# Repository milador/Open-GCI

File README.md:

# Open-GCI

An open-source accessible gaming interface that enables those with limited or no hand movement to play their favourite console based game using more accessible input methods.
Adaptive switches and USB keyboards are currently the two input methods that can be used to play console based games.

# Downloads 

These are all the files and documentation associated with the Open-GCI project.

 <table style="width:100%">
  <tr>
    <th>Resource</th>
    <th>Version</th>
    <th>Format</th>
    <th>Link</th>
  </tr>
    <tr>
    <td>Open-GCI All</td>
    <td>1.0</td>
    <td>ZIP</td>
    <td><a href="https://github.com/milador/Open-GCI/archive/master.zip">Open-GCI-master.zip</a></td>
  </tr>
  <tr>
    <td>Open-GCI Manual</td>
    <td></td>
    <td>PDF</td>
    <td></td>
  </tr>
  <tr>
    <td>Open-GCI BOM (XLSX)</td>
    <td>October 6, 2018</td>
    <td>XLSX</td>
    <td><a href="https://github.com/milador/Open-GCI/raw/master/Open-GCI_BOM.xlsx">Open-GCI_BOM.xlsx</a></td>
  </tr>
  <tr>
    <td>Open-GCI Keyboard code</td>
    <td>1.0</td>
    <td>Py</td>
    <td><a href="https://github.com/milador/Open-GCI/raw/master/Software/gci_keyboard.py">gci_keyboard.py</a></td>
  </tr>
  <tr>
    <td>Open-GCI Board Layout</td>
    <td>1.0</td>
    <td>BRD</td>
    <td><a href="https://raw.githubusercontent.com/milador/Open-GCI/master/Hardware/PCB_design/Open-GCI.brd">Open-GCI.brd</a></td>
  </tr>
  <tr>
    <td>Open-GCI Board Schematic</td>
    <td>1.0</td>
    <td>SCH</td>
    <td><a href="https://raw.githubusercontent.com/milador/Open-GCI/master/Hardware/PCB_design/Open-GCI.sch">Open-GCI.sch</a></td>
  </tr>
</table> 

# Diagram

The following diagram represents the hardware of the Open-GCI interface.

# Installation 

## Hardware Setup Instructions

Coming soon..

## Software Setup Instructions

  1. Install Raspbian on an SD card according to the official documents 

https://www.raspberrypi.org/documentation/installation/installing-images/

2.	Download Dependencies

  2.1. Startup the raspberrypi zero W
  
  2.2. Open the command line
  
  2.3. Install the necessary packages
```
sudo apt-get update
sudo apt-get install build-essential python-dev python-pip git scons swig
sudo pip install RPi.GPIO
```

3.	Compile & Install rpi_ws281x Library
  
  3.1. Download the library source and compile it using following command : 
``` 
git clone https://github.com/jgarff/rpi_ws281x.git
cd rpi_ws281x
scons
``` 
  3.2. Install the Python library by executing following command : 
``` 
cd python
sudo python setup.py install
``` 
  
4.	Download gci_keyboard.py
  
  4.1. Open the command line
  
  4.2. Enter the pi directory
  
  4.3. Create a new python file using nano and name it gci_keyboard.py using following command: ```sudo nano gci_keyboar.py``` 
  
  4.4. Copy and paste the keyboard code from Software/gci_keyboard.py 
  
  4.5. Save the file and exit nano
  
5. Run code on bootup

  5.1. Open /etc/rc.local using nano by running following command: ```sudo nano /etc/rc.local```
  
  5.2. Add the following line on its own line right before exit 0: ```sudo python /home/pi/gci_keyboard.py  &```
  
  5.3. Save and exit /etc/rc.local
  
  5.4. Reboot the raspberrypi zero W by running following command: ```sudo shutdown -r now```
  
6.	Varify software is running 
  
   6.1. The Led will change color from Blue to Green when the software is ready to use

# PS4 to keyboard button mapping 

# Picture 

# License

## Creative Commons Attribution-NonCommercial-ShareAlike (CC-BY-NC-SA)

Copyright (c) 2018 Milador

A creative commons license that bans commercial use and requires you to release any modified works under this license.

<br />This work is licensed under a <a rel="license" href="http://creativecommons.org/licenses/by-nc-sa/3.0/">Creative Commons Attribution-NonCommercial-ShareAlike 3.0 Unported License</a>.

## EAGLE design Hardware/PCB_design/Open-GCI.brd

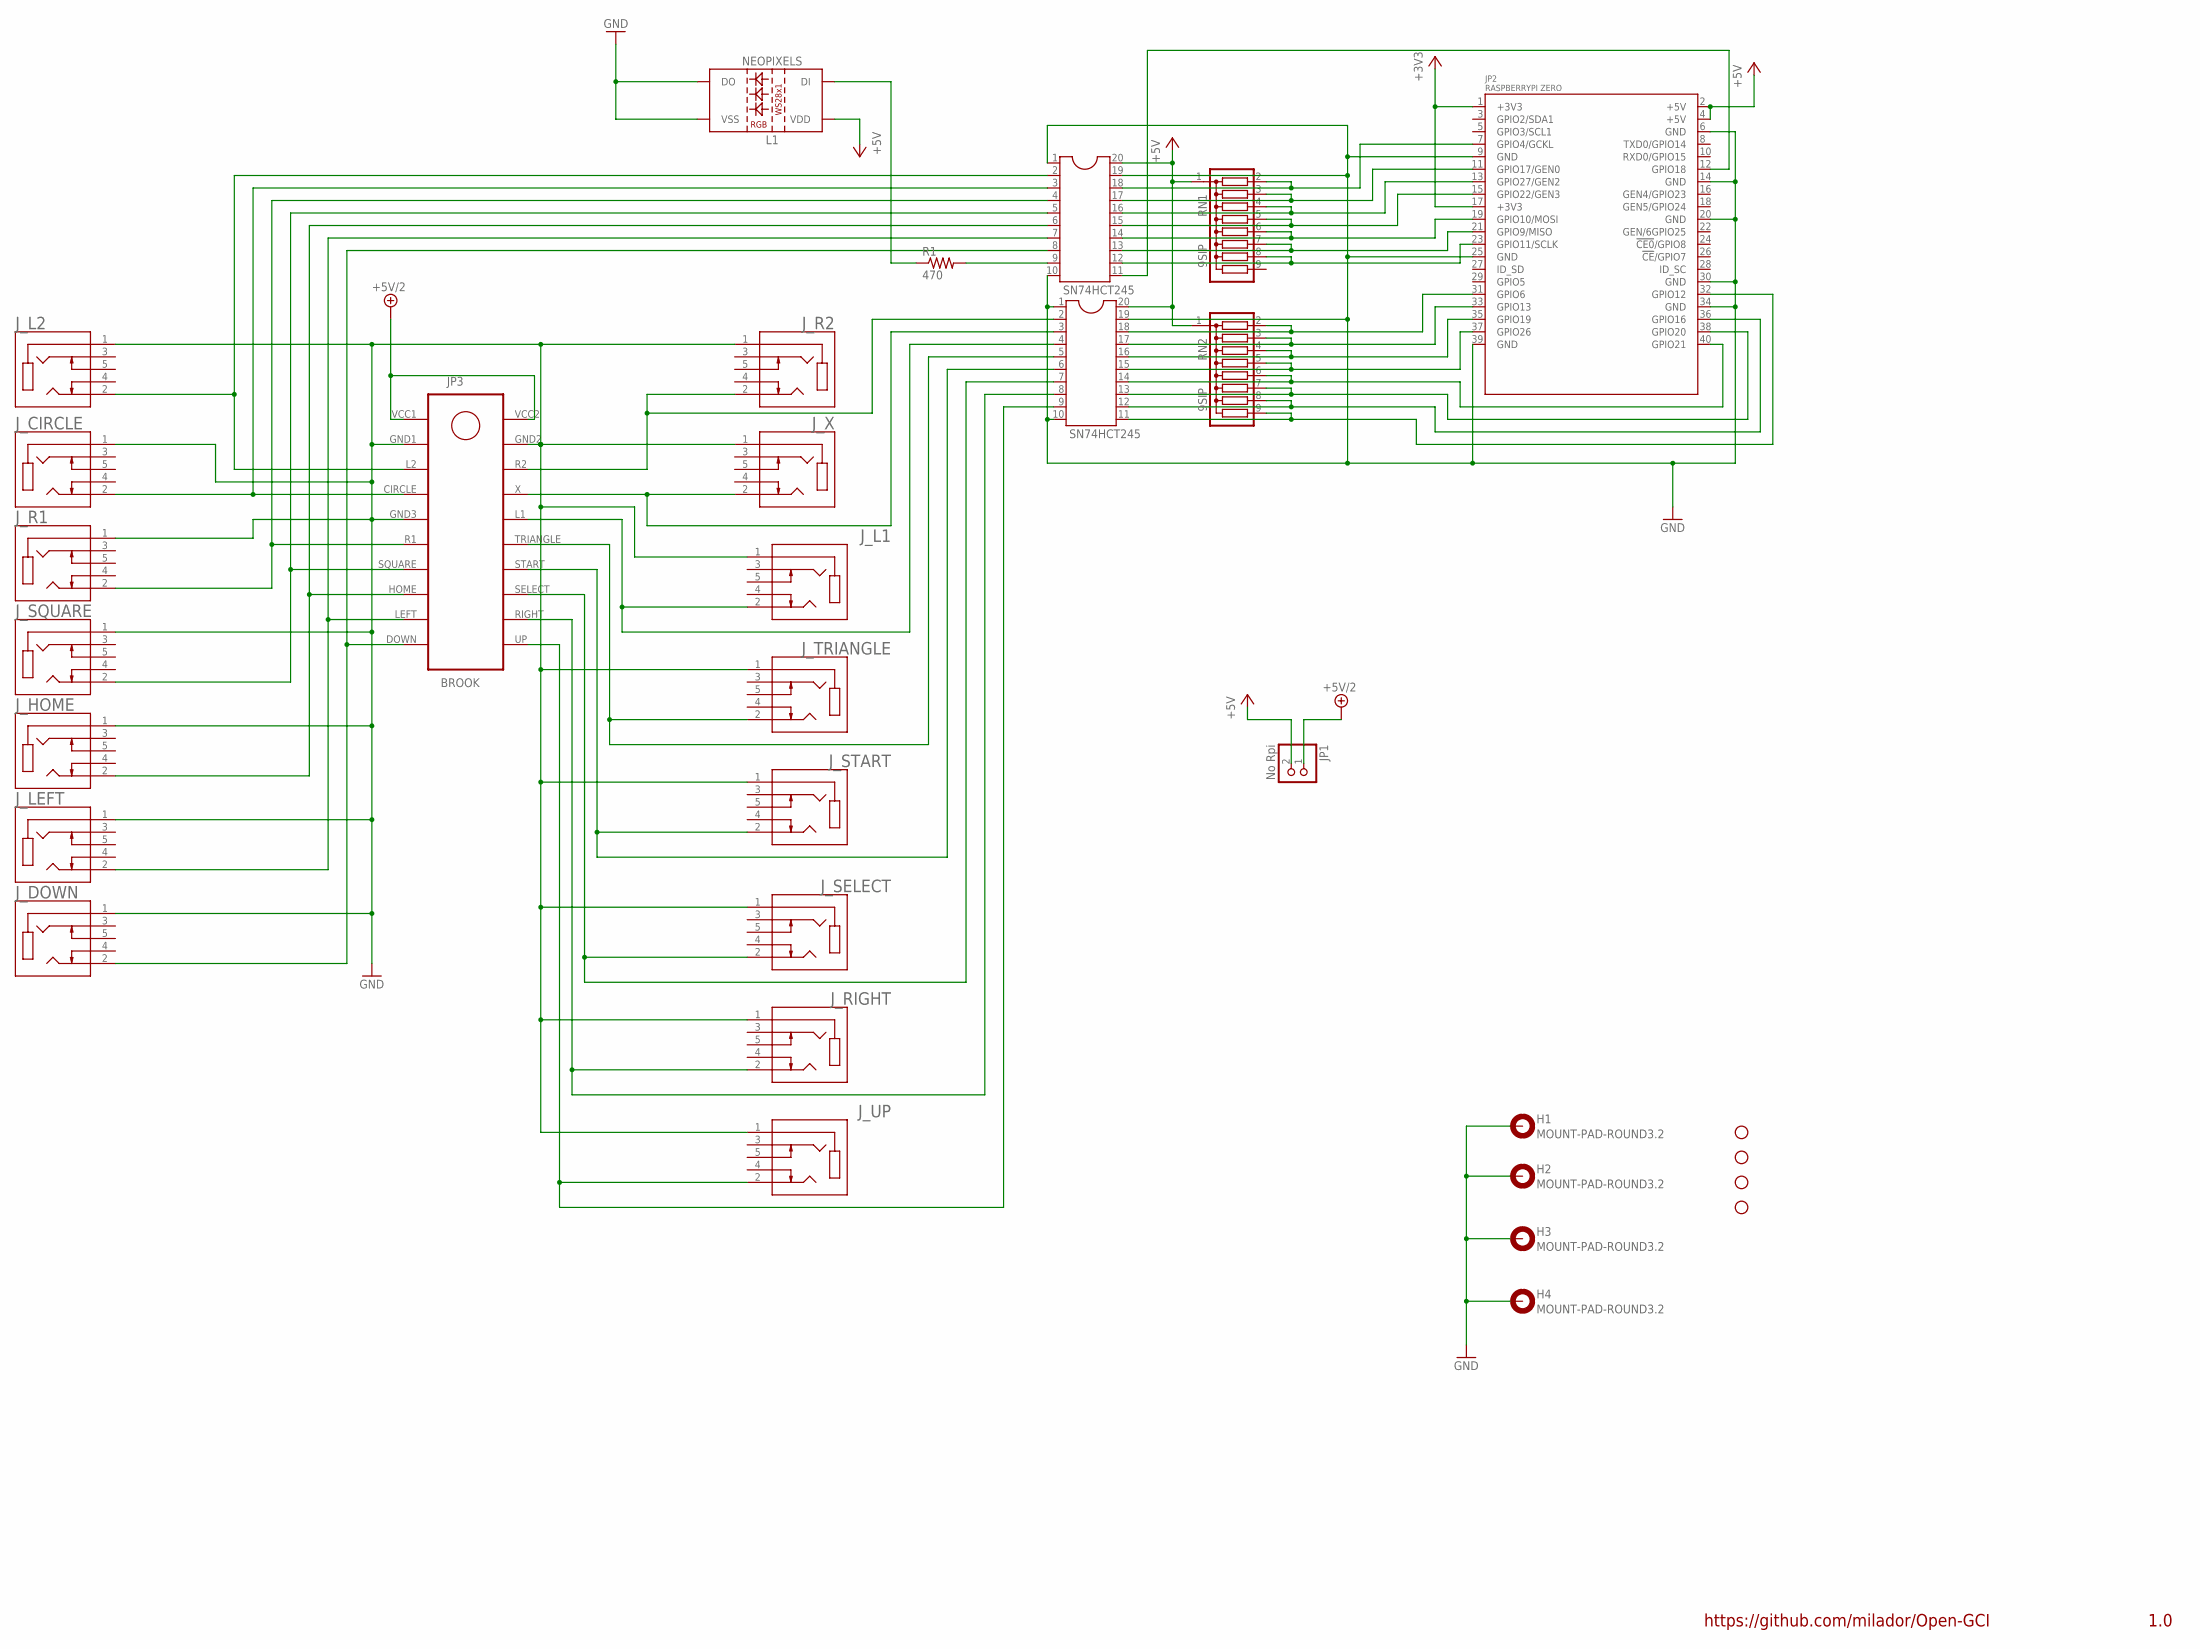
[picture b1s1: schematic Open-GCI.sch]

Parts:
H1, H2, H3, H4: MOUNT-PAD-ROUND3.2; 3,2-PAD
H5, H6, H7, H8: STAND-OFF
IC1, IC2: SN74HCT245
JP1: No Rpi; 1X02
JP2: RASPBERRYPI ZERO; RASPBERRYPI_ZERO
JP3: BROOK; CONN_2X10
J_CIRCLE: SJ1-3535NG; CUI_SJ1-3535NG
J_DOWN: SJ1-3535NG; CUI_SJ1-3535NG
J_HOME: SJ1-3535NG; CUI_SJ1-3535NG
J_L1, J_L2: SJ1-3535NG; CUI_SJ1-3535NG
J_LEFT: SJ1-3535NG; CUI_SJ1-3535NG
J_R1, J_R2: SJ1-3535NG; CUI_SJ1-3535NG
J_RIGHT: SJ1-3535NG; CUI_SJ1-3535NG
J_SELECT: SJ1-3535NG; CUI_SJ1-3535NG
J_SQUARE: SJ1-3535NG; CUI_SJ1-3535NG
J_START: SJ1-3535NG; CUI_SJ1-3535NG
J_TRIANGLE: SJ1-3535NG; CUI_SJ1-3535NG
J_UP: SJ1-3535NG; CUI_SJ1-3535NG
J_X: SJ1-3535NG; CUI_SJ1-3535NG
L1: NEOPIXELS; NEOPIXELS-5MM
R1: 470; 0204/7
RN1, RN2: 9SIP; SIL9

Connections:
+3V3: JP2.1 (+3V3), JP2.17 (+3V3)
+5V: IC1.20, IC2.20, JP1.2, JP2.2 (+5V), JP2.4 (+5V), L1.2 (VDD), RN1.1, RN2.1
+5V/2: JP1.1, JP3.VCC1, JP3.VCC2
GND: H1.B3,2, H2.B3,2, H3.B3,2, H4.B3,2, IC1.1, IC1.10, IC1.19, IC2.1, IC2.10, IC2.19, JP2.6 (GND), JP2.9 (GND), JP2.14 (GND), JP2.20 (GND), JP2.25 (GND), JP2.30 (GND), JP2.34 (GND), JP2.39 (GND), JP3.GND1, JP3.GND2, JP3.GND3, J_CIRCLE.1, J_DOWN.1, J_HOME.1, J_L1.1, J_L2.1, J_LEFT.1, J_R1.1, J_R2.1, J_RIGHT.1, J_SELECT.1, J_SQUARE.1, J_START.1, J_TRIANGLE.1, J_UP.1, J_X.1, L1.3 (VSS), L1.4 (DO)
unnamed: IC1.9, R1.2
unnamed: L1.1 (DI), R1.1
NGP7: IC1.18, JP2.7 (GPIO4/GCKL), RN1.2
NGP11: IC1.17, JP2.11 (GPIO17/GEN0), RN1.3
NGP12: IC1.11, JP2.12 (GPIO18)
NGP13: IC1.16, JP2.13 (GPIO27/GEN2), RN1.4
NGP15: IC1.15, JP2.15 (GPIO22/GEN3), RN1.5
NGP19: IC1.14, JP2.19 (GPIO10/MOSI), RN1.6
NGP21: IC1.13, JP2.21 (GPIO9/MISO), RN1.7
NGP23: IC1.12, JP2.23 (GPIO11/SCLK), RN1.8
NGP31: IC2.18, JP2.31 (GPIO6), RN2.2
NGP32: IC2.11, JP2.32 (GPIO12), RN2.9
NGP33: IC2.17, JP2.33 (GPIO13), RN2.3
NGP35: IC2.16, JP2.35 (GPIO19), RN2.4
NGP36: IC2.12, JP2.36 (GPIO16), RN2.8
NGP37: IC2.15, JP2.37 (GPIO26), RN2.5
NGP38: IC2.13, JP2.38 (GPIO20), RN2.7
NGP40: IC2.14, JP2.40 (GPIO21), RN2.6
NJ_CIR: IC1.3, JP3.CIRCLE, J_CIRCLE.2
NJ_DOWN: IC1.8, JP3.DOWN, J_DOWN.2
NJ_HOME: IC1.6, JP3.HOME, J_HOME.2
NJ_L1: IC2.4, JP3.L1, J_L1.2
NJ_L2: IC1.2, JP3.L2, J_L2.2
NJ_LEFT: IC1.7, JP3.LEFT, J_LEFT.2
NJ_R1: IC1.4, JP3.R1, J_R1.2
NJ_R2: IC2.2, JP3.R2, J_R2.2
NJ_RIGHT: IC2.8, JP3.RIGHT, J_RIGHT.2
NJ_SELECT: IC2.7, JP3.SELECT, J_SELECT.2
NJ_SQU: IC1.5, JP3.SQUARE, J_SQUARE.2
NJ_START: IC2.6, JP3.START, J_START.2
NJ_TRI: IC2.5, JP3.TRIANGLE, J_TRIANGLE.2
NJ_UP: IC2.9, JP3.UP, J_UP.2
NJ_X: IC2.3, JP3.X, J_X.2

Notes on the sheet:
https://github.com/milador/Open-GCI
1.0

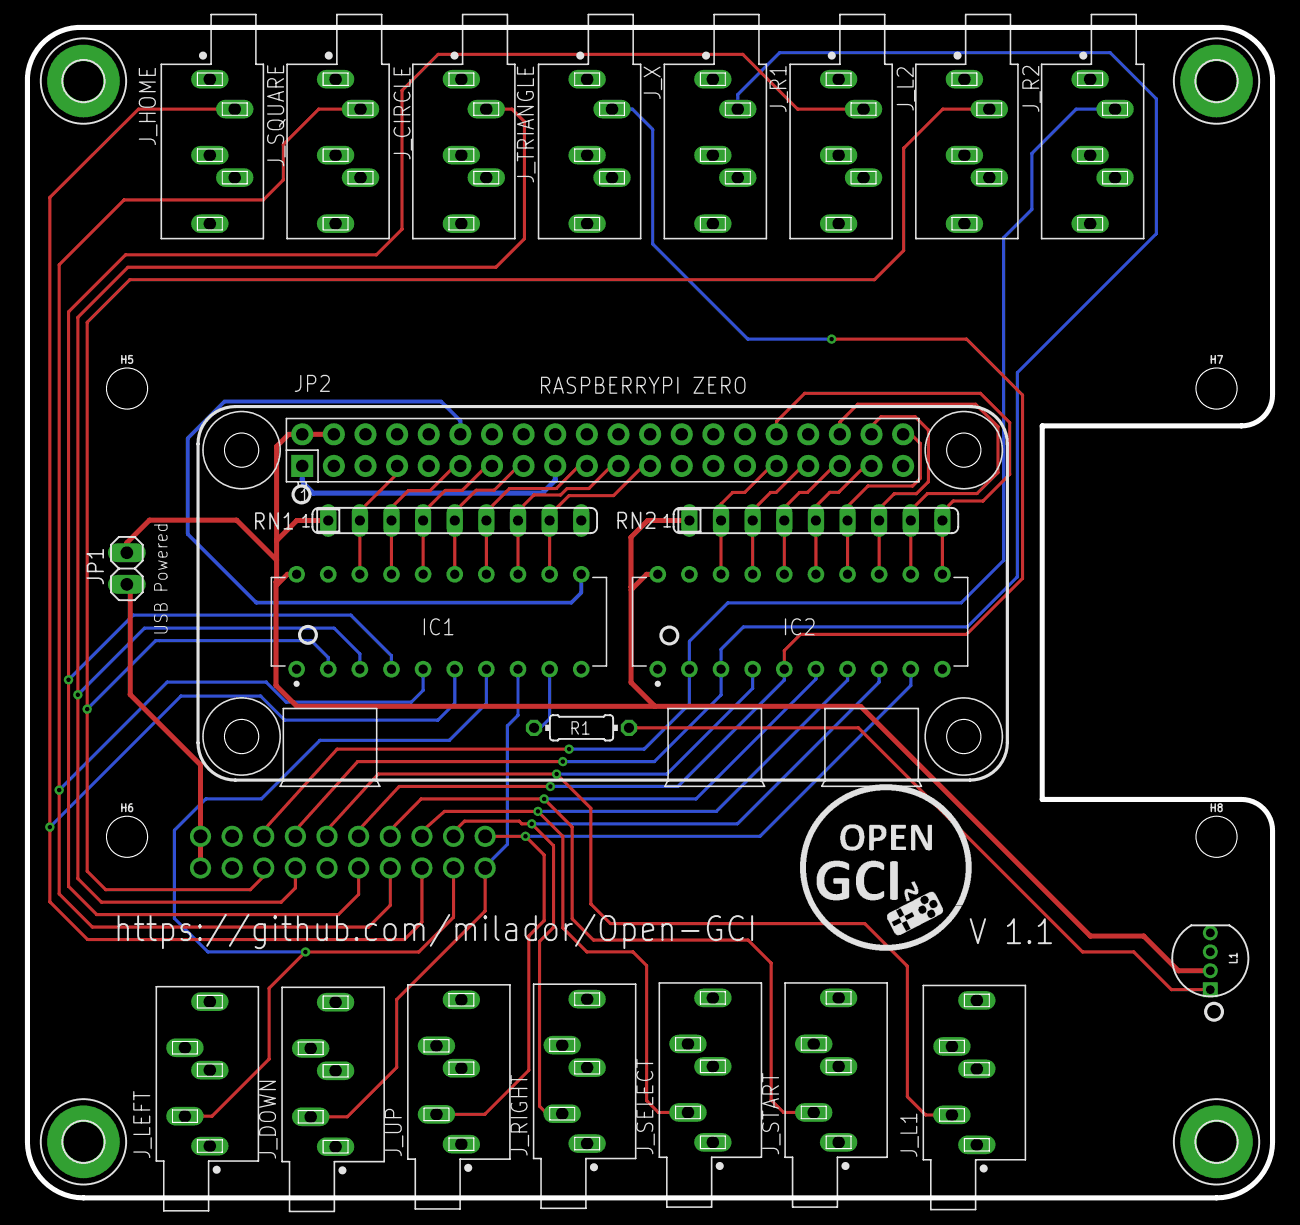
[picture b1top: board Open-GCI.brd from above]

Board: 2 copper layers, 100.0 x 94.0 mm, 32 parts (1 on the bottom side), 37 nets.

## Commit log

2018-09-21 Added the readme file
2018-09-21 Updated Readme file
2018-10-07 Added part list and the PCB file
2018-10-07 Added the hardware diagram
2018-10-07 Updated the readme
2018-10-07 Added the keyboard software
2018-10-07 Updated the schematics
2018-10-07 Added downloads section
2018-10-07 Added the software installation
2018-10-07 Added ps4 to keyboard mapping
2018-10-21 Fixed the 3.5mm jack issue
2018-11-04 Long press button feature through Rpi GPIOs is added.
2020-06-16 Updated PCB, Component listand gerber files
2021-02-26 Added license
2021-02-26 Create LICENSE

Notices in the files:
parts and their libraries:
SparkFun-Hardware: Licensing: Creative Commons ShareAlike 4.0 International - https://creativecommons.org/licenses/by-sa/4.0
